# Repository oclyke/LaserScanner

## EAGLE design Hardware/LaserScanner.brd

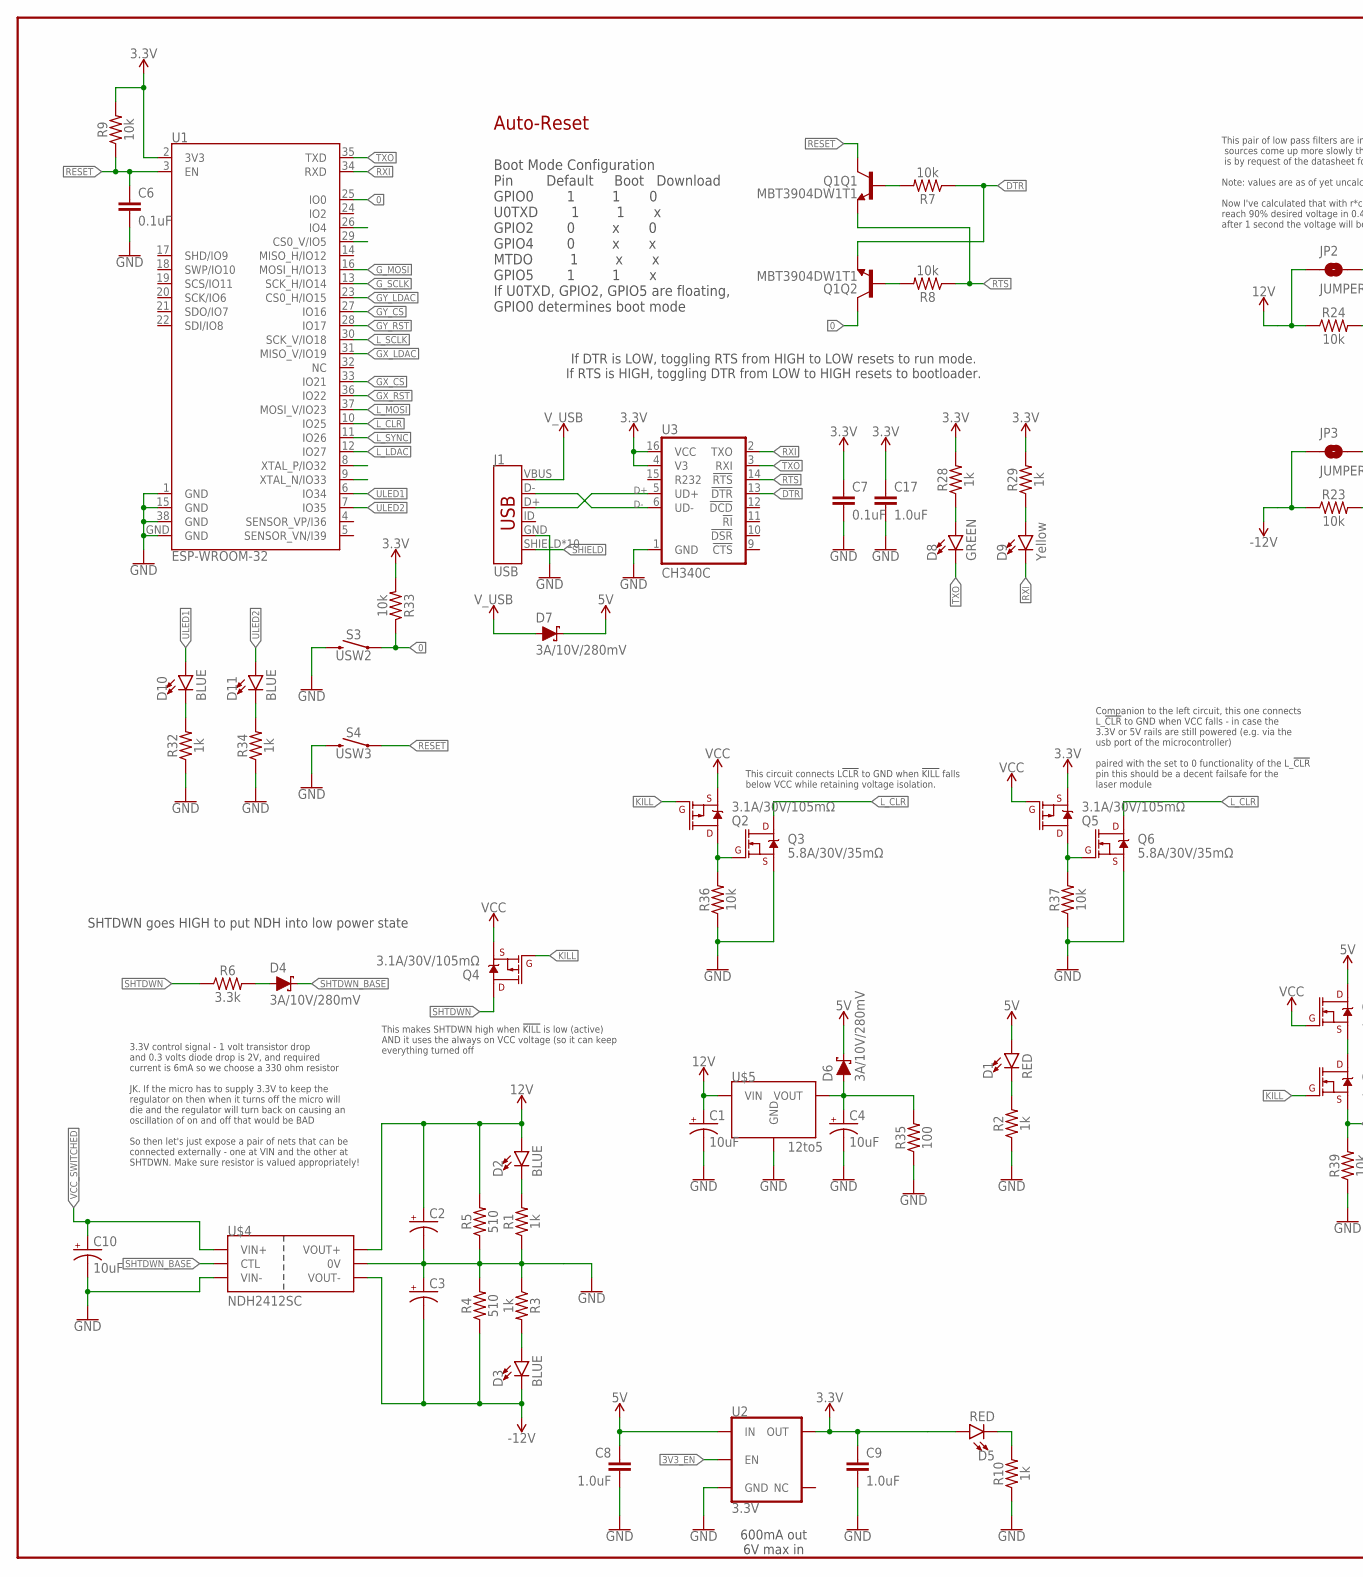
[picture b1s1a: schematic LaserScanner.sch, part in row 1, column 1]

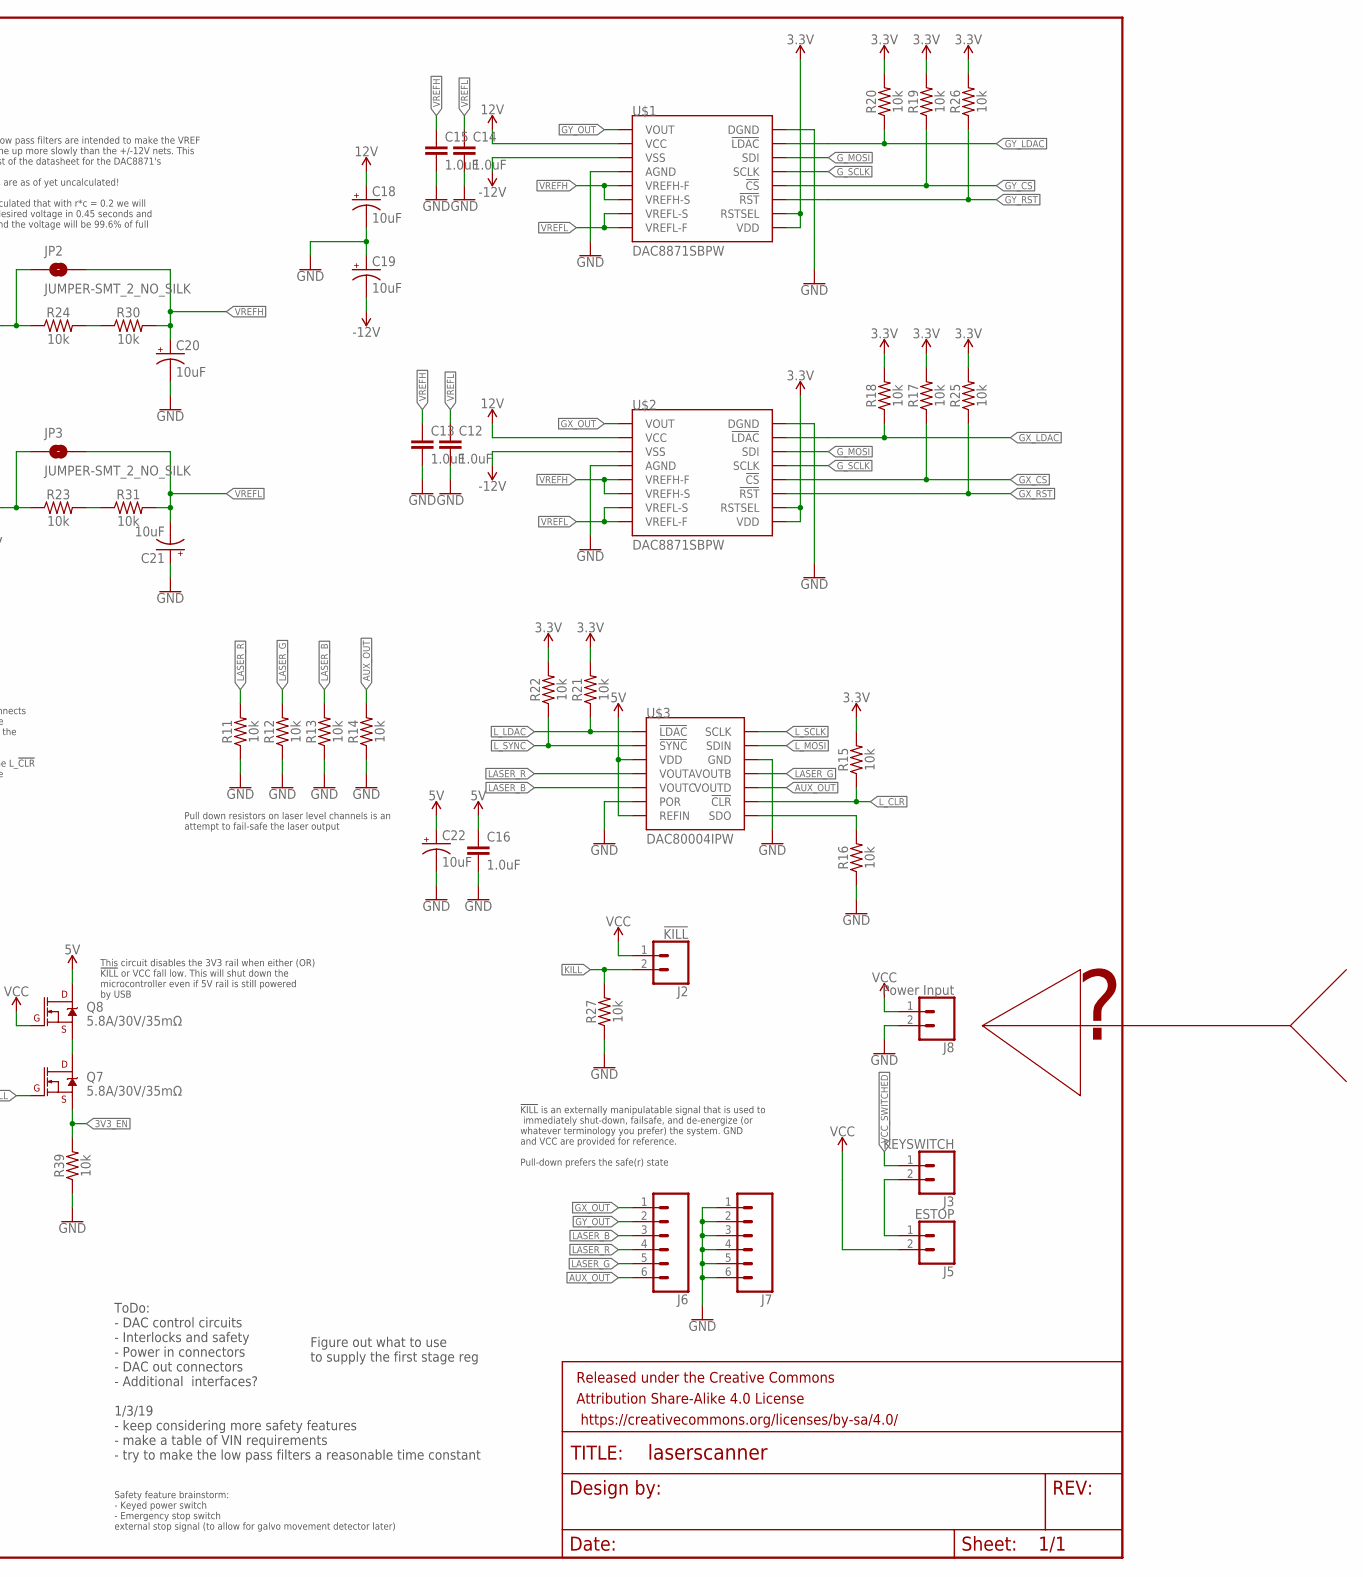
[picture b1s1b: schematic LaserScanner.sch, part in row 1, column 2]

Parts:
C1, C4, C10, C18, C19, C20, C21, C22: 10uF; EIA3216
C2, C3: 47UF-POLAR-PANASONIC_D-50V-20%; PANASONIC_D
C6, C7: 0.1uF; 0603
C8, C9, C12, C13, C14, C15, C16, C17: 1.0uF; 0603
D1, D5: RED; LED-0603
D2, D3, D10, D11: BLUE; LED-0603
D4, D6, D7: 3A/10V/280mV; SOD-323
D8: GREEN; LED-0603
D9: Yellow; LED-0603
FRAME1: FRAME-LEDGER; CREATIVE_COMMONS
J1: USB; USB-MICROB-PTH-MILL
J2: !KILL!; 1X02_NO_SILK
J3: KEYSWITCH; 1X02_NO_SILK
J5: ESTOP; 1X02_NO_SILK
J6, J7: CONN_06NO_SILK_FEMALE_PTH; 1X06_NO_SILK
J8: Power Input; 1X02_NO_SILK
JP2, JP3: JUMPER-SMT_2_NO_SILK; SMT-JUMPER_2_NO_SILK
Q1: MBT3904DW1T1; SC70-6
Q2, Q4, Q5: 3.1A/30V/105mΩ; SOT23-3
Q3, Q6, Q7, Q8: 5.8A/30V/35mΩ; SOT23-3
R1, R2, R3, R10, R28, R29, R32, R34: 1k; 0603
R4, R5: 510; 2010
R6: 3.3k; 0603
R7, R8, R9, R11, R12, R13, R14, R15, R16, R17, R18, R19, R20, R21, R22, R23, R24, R25, R26, R27, R30, R31, R33, R36, R37, R39: 10k; 0603
R35: 100; 0603
S3: USW2; TACTILE_SWITCH_SMD_5.2MM
S4: USW3; TACTILE_SWITCH_SMD_5.2MM
U1: ESP-WROOM-32
U2: 3.3V; SOT23-5
U3: CH340C; SO016
U$1, U$2: DAC8871SBPW; TSSOP16
U$3: DAC80004IPW; TSSOP14
U$4: NDH2412SC; NDH
U$5: 12to5; RE-78E

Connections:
0: Q1.6 (C), R33.1, S3.1, S3.2 (1), U1.25 (IO0)
3.3V: C7.1, C9.1, C17.1, D5.A, Q5.2 (S), R9.2, R15.2, R17.2, R18.2, R19.2, R20.2, R21.2, R22.2, R25.2, R26.2, R28.2, R29.2, R33.2, U1.2 (3V3), U2.5 (OUT), U3.4 (V3), U3.16 (VCC), U$1.9 (VDD), U$1.10 (RSTSEL), U$2.9 (VDD), U$2.10 (RSTSEL)
3V3_EN: Q7.2 (S), R39.2, U2.3 (EN)
5V: C8.1, C16.1, C22.+, D1.A, D6.C, D7.C, Q8.3 (D), U2.1 (IN), U$3.3 (VDD), U$3.7 (REFIN)
12V: C1.+, C2.+, C18.+, D2.A, JP2.1, R5.2, R24.1, U$1.2 (VCC), U$2.2 (VCC), U$4.6 (VOUT+), U$5.1 (VIN)
!DTR: Q1.1 (E), R7.1, U3.13 (!DTR)
!KILL: J2.2, Q2.1 (G), Q4.1 (G), Q7.1 (G), R27.2
!RTS: Q1.4 (E), R8.1, U3.14 (!RTS)
-12V: C3.-, C19.-, D3.C, JP3.1, R4.1, R23.1, U$1.3 (VSS), U$2.3 (VSS), U$4.9 (VOUT-)
AUX_OUT: J6.6, R14.2, U$3.10 (VOUTD)
D+: J1.D+, U3.5 (UD+)
D-: J1.D-, U3.6 (UD-)
GND: C1.-, C2.-, C3.+, C4.-, C6.2, C7.2, C8.2, C9.2, C10.-, C12.2, C13.2, C14.2, C15.2, C16.2, C17.2, C18.-, C19.+, C20.-, C21.+, C22.-, J1.GND, J7.1, J7.2, J7.3, J7.4, J7.5, J7.6, J8.2, Q3.2 (S), Q6.2 (S), R1.1, R2.1, R3.1, R4.2, R5.1, R10.1, R11.1, R12.1, R13.1, R14.1, R16.1, R27.1, R32.1, R34.1, R35.1, R36.1, R37.1, R39.1, S3.3 (2), S3.4 (2), S4.3 (2), S4.4 (2), U1.1 (GND), U1.15 (GND), U1.38 (GND), U1.GND, U2.2 (GND), U3.1 (GND), U$1.4 (AGND), U$1.16 (DGND), U$2.4 (AGND), U$2.16 (DGND), U$3.6 (POR), U$3.12 (GND), U$4.1 (VIN-), U$4.7 (0V), U$5.2 (GND)
GX_!CS: R17.1, U1.33 (IO21), U$2.12 (!CS)
GX_!LDAC: R18.1, U1.31 (MISO_V/IO19), U$2.15 (!LDAC)
GX_!RST: R25.1, U1.36 (IO22), U$2.11 (!RST)
GX_OUT: J6.1, U$2.1 (VOUT)
GY_!CS: R19.1, U1.27 (IO16), U$1.12 (!CS)
GY_!LDAC: R20.1, U1.23 (CS0_H/IO15), U$1.15 (!LDAC)
GY_!RST: R26.1, U1.28 (IO17), U$1.11 (!RST)
GY_OUT: J6.2, U$1.1 (VOUT)
G_MOSI: U1.16 (MOSI_H/IO13), U$1.14 (SDI), U$2.14 (SDI)
G_SCLK: U1.13 (SCK_H/IO14), U$1.13 (SCLK), U$2.13 (SCLK)
LASER_B: J6.3, R13.2, U$3.5 (VOUTC)
LASER_G: J6.5, R12.2, U$3.11 (VOUTB)
LASER_R: J6.4, R11.2, U$3.4 (VOUTA)
L_!CLR: Q3.3 (D), Q6.3 (D), R15.1, U1.10 (IO25), U$3.9 (!CLR)
L_!LDAC: R21.1, U1.12 (IO27), U$3.1 (!LDAC)
L_!SYNC: R22.1, U1.11 (IO26), U$3.2 (!SYNC)
L_MOSI: U1.37 (MOSI_V/IO23), U$3.13 (SDIN)
L_SCLK: U1.30 (SCK_V/IO18), U$3.14 (SCLK)
unnamed: D1.C, R2.2
unnamed: R16.2, U$3.8 (SDO)
unnamed: D2.C, R1.2
unnamed: D4.A, R6.2
unnamed: D3.A, R3.2
unnamed: D5.C, R10.2
unnamed: C4.+, D6.A, R35.2, U$5.3 (VOUT)
unnamed: J3.2, J5.1
unnamed: Q1.5 (B), R7.2
unnamed: Q1.2 (B), R8.2
unnamed: D8.A, R28.1
unnamed: D9.A, R29.1
unnamed: R24.2, R30.1
unnamed: R23.2, R31.1
unnamed: D10.C, R32.2
unnamed: D11.C, R34.2
unnamed: Q2.3 (D), Q3.1 (G), R36.2
unnamed: Q5.3 (D), Q6.1 (G), R37.2
unnamed: Q7.3 (D), Q8.2 (S)
RESET: C6.1, Q1.3 (C), R9.1, S4.1, S4.2 (1), U1.3 (EN)
RXI: D9.C, U1.34 (RXD), U3.2 (TXO)
SHIELD: J1.SHIELD, J1.SHIELD2 (SHIELD), J1.SHIELD3 (SHIELD), J1.SHIELD4 (SHIELD), J1.SHIELD5 (SHIELD), J1.SHIELD6 (SHIELD), J1.SHIELD7 (SHIELD), J1.SHIELD8 (SHIELD), J1.SHIELD9 (SHIELD), J1.SHIELD10 (SHIELD)
SHTDWN: Q4.3 (D), R6.1
SHTDWN_BASE: D4.C, U$4.3 (CTL)
TXO: D8.C, U1.35 (TXD), U3.3 (RXI)
ULED1: D10.A, U1.6 (IO34)
ULED2: D11.A, U1.7 (IO35)
VCC: J2.1, J5.2, J8.1, Q2.2 (S), Q4.2 (S), Q5.1 (G), Q8.1 (G)
VCC_SWITCHED: C10.+, J3.1, U$4.2 (VIN+)
VREFH: C13.1, C15.1, C20.+, JP2.2, R30.2, U$1.5 (VREFH-F), U$1.6 (VREFH-S), U$2.5 (VREFH-F), U$2.6 (VREFH-S)
VREFL: C12.1, C14.1, C21.-, JP3.2, R31.2, U$1.7 (VREFL-S), U$1.8 (VREFL-F), U$2.7 (VREFL-S), U$2.8 (VREFL-F)
V_USB: D7.A, J1.VBUS

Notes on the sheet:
Boot Mode Configuration Pin Default Boot Download GPIO0 1 1 0 U0TXD 1 1 x GPIO2 0 x 0 GPIO4 0 x x MTDO 1 x x GPIO5 1 1 x If U0TXD, GPIO2, GPIO5 are floating, GPIO0 determines boot mode
If DTR is LOW, toggling RTS from HIGH to LOW resets to run mode. If RTS is HIGH, toggling DTR from LOW to HIGH resets to bootloader.
Auto-Reset
ToDo: - DAC control circuits - Interlocks and safety - Power in connectors - DAC out connectors - Additional interfaces? 1/3/19 - keep considering more safety features - make a table of VIN requirements - try to make the low pass filters a reasonable time constant
SHTDWN goes HIGH to put NDH into low power state
Figure out what to use to supply the first stage reg
600mA out 6V max in
3.3V control signal - 1 volt transistor drop and 0.3 volts diode drop is 2V, and required current is 6mA so we choose a 330 ohm resistor JK. If the micro has to supply 3.3V to keep the regulator on then when it turns off the micro will die and the regulator will turn back on causing an oscillation 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
Safety feature brainstorm: - Keyed power switch - Emergency stop switch external stop signal (to allow for galvo movement detector later)
Pull down resistors on laser level channels is an attempt to fail-safe the laser output
This pair of low pass filters are intended to make the VREF sources come up more slowly than the +/-12V nets. This is by request of the datasheet for the DAC8871's Note: values are as of yet uncalculated! Now I've calculated that with r*c = 0.2 we will reach 90% desired voltage in 0.45 seconds and 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
This makes SHTDWN high when !KILL! is low (active) AND it uses the always on VCC voltage (so it can keep everything turned off
!KILL! is an externally manipulatable signal that is used to immediately shut-down, failsafe, and de-energize (or whatever terminology you prefer) the system. GND and VCC are provided for reference. Pull-down prefers the safe(r) state
This circuit connects L!CLR! to GND when !KILL! falls below VCC while retaining voltage isolation.
Companion to the left circuit, this one connects L_!CLR! to GND when VCC falls - in case the 3.3V or 5V rails are still powered (e.g. via the usb port of the microcontroller) paired with the set to 0 functionality of the L_!CLR! pin this should be a decent failsafe for the laser module
This circuit disables the 3V3 rail when either (OR) !KILL! or VCC fall low. This will shut down the microcontroller even if 5V rail is still powered by USB

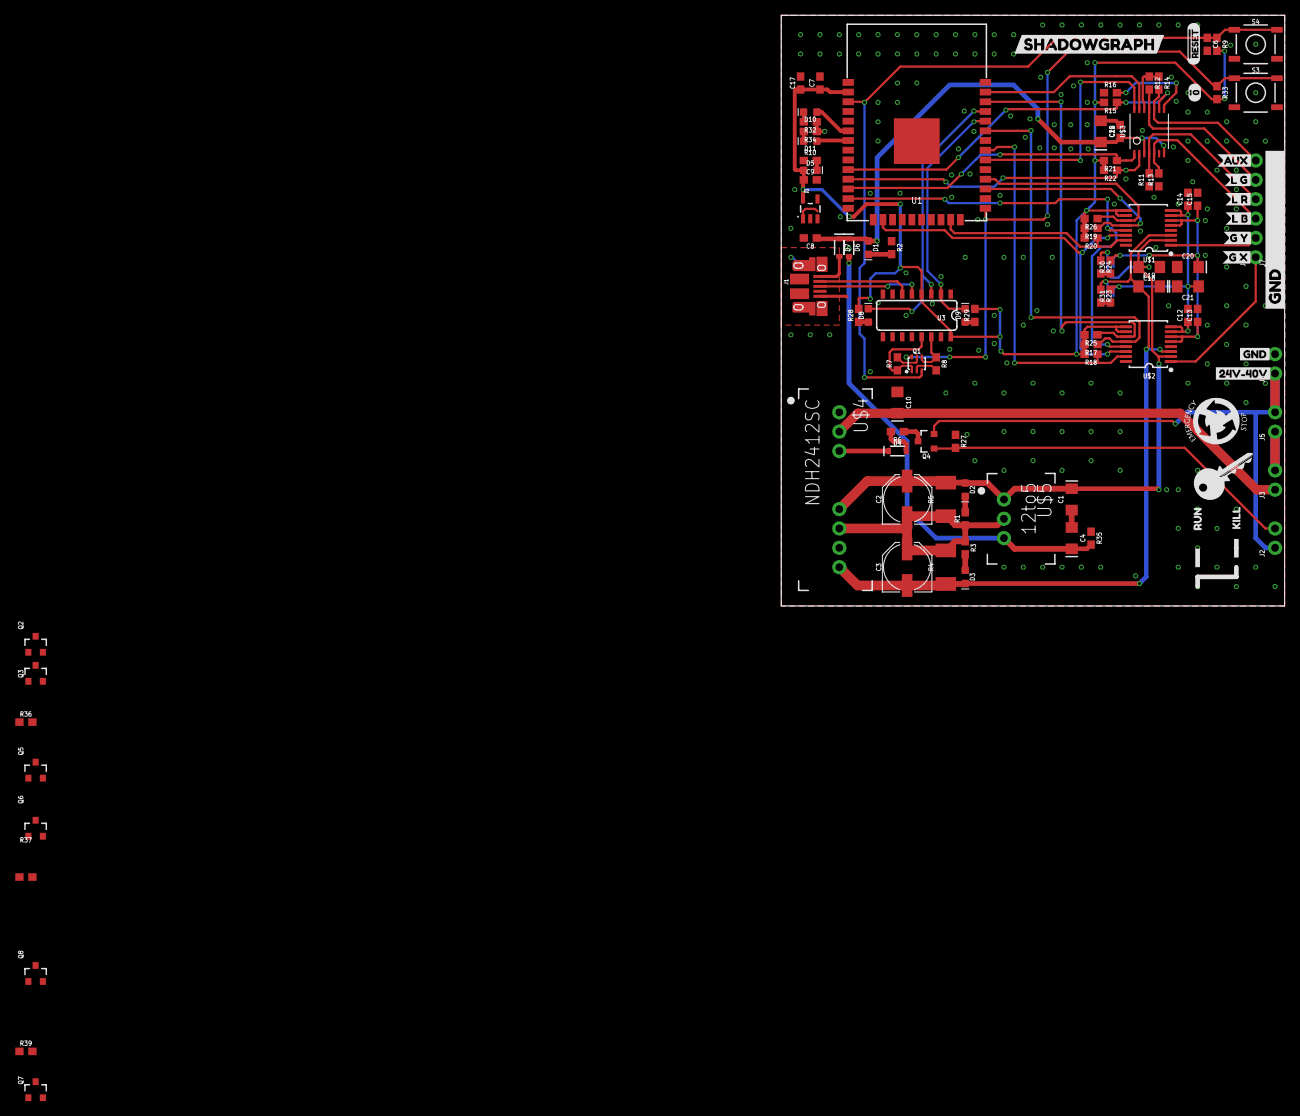
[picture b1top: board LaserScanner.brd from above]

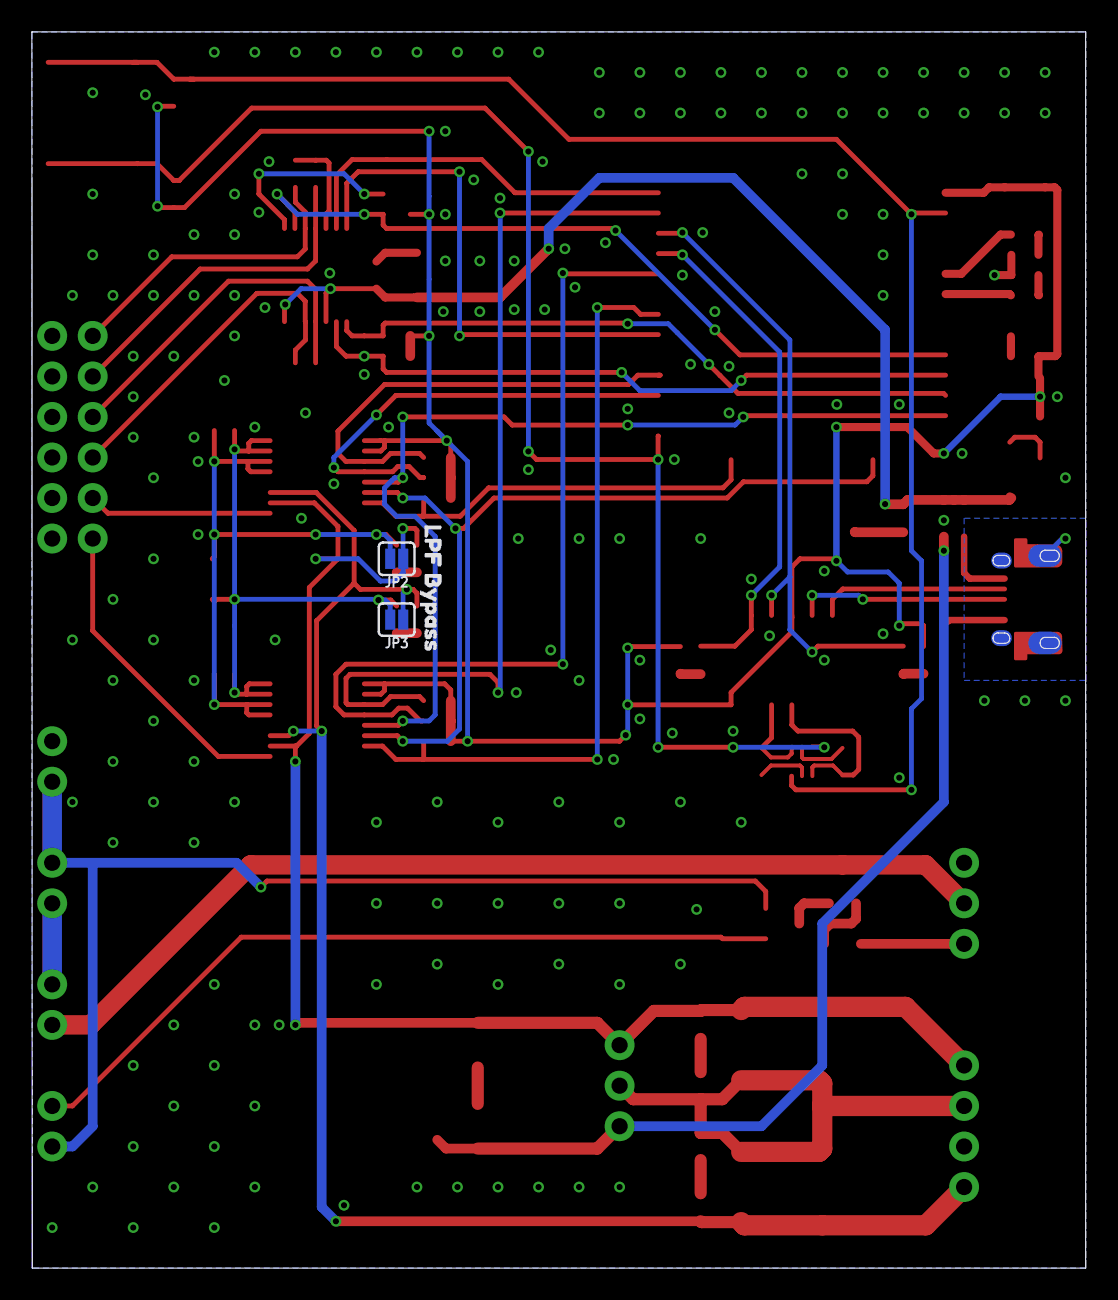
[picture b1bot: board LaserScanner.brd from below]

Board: 2 copper layers, 66.0 x 77.4 mm, 114 parts (3 on the bottom side), 63 nets.

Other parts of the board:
U$6: KEY#PNG
U$7: E#STOP#JPG
U$8: 24V#40V3
U$9: GND0
U$10: GND1
U$11: KILL11
U$12: RUN10
U$13: #RESET14
U$14: #013
U$15: AUX4
U$16: G_X14
U$17: G_Y13
U$18: L_B12
U$19: LPF_BYPASS12
U$20: L_R14
U$21: L_G10
U$22: SHADOWGRAPH15

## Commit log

2018-12-15 Add power supply and ESP32
    Power supply doesn't have a source yet though
2019-01-04 Added DAC circuits and power interlocks
2019-01-04 Add KILL signal and VREF delay
2019-01-15 Pushing local changes so that they are accessible from home
2019-01-15 RC calculations
2019-01-16 Push to work from laptop
2019-01-17 Made a significant push on routing the board
2019-01-17 Added silk, optimized ground planes, and cammed
2019-01-18 Panelized, cammed, and ordered
2019-10-22 stop using input only pins for led outputs
2019-10-22 add DA80004 test based on ESP32 hello world
2019-10-26 add DAX0004 submodule
2019-10-26 get main example working
2019-10-27 add development branch of DA80004 ESP32 test
2019-10-27 Add DAC8871 unit test for ESP32
2019-11-01 move dax8004 unit test
2019-11-01 move DA80004 unit test
2021-08-14 remove backup files
2021-08-14 add failsafes to schematic
    failsafes include:
    - pulling the laser dac clr line to gnd if kill_n goes low or if VCC is interrupted (can be used to safe the laser)
    - disabling the 3.3V rail (effectively stopping laser output and microcontroller) when kill_n or VCC go low (allowing external kill and interlocks to make safe even when USB is powering 5V rail)
    todo: routing

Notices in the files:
parts and their libraries:
SparkFun-Capacitors: Licensing: Creative Commons ShareAlike 4.0 International - https://creativecommons.org/licenses/by-sa/4.0
SparkFun-Aesthetics: Released under the Creative Commons Attribution Share-Alike 4.0 License
SparkFun-Aesthetics: https://creativecommons.org/licenses/by-sa/4.0
